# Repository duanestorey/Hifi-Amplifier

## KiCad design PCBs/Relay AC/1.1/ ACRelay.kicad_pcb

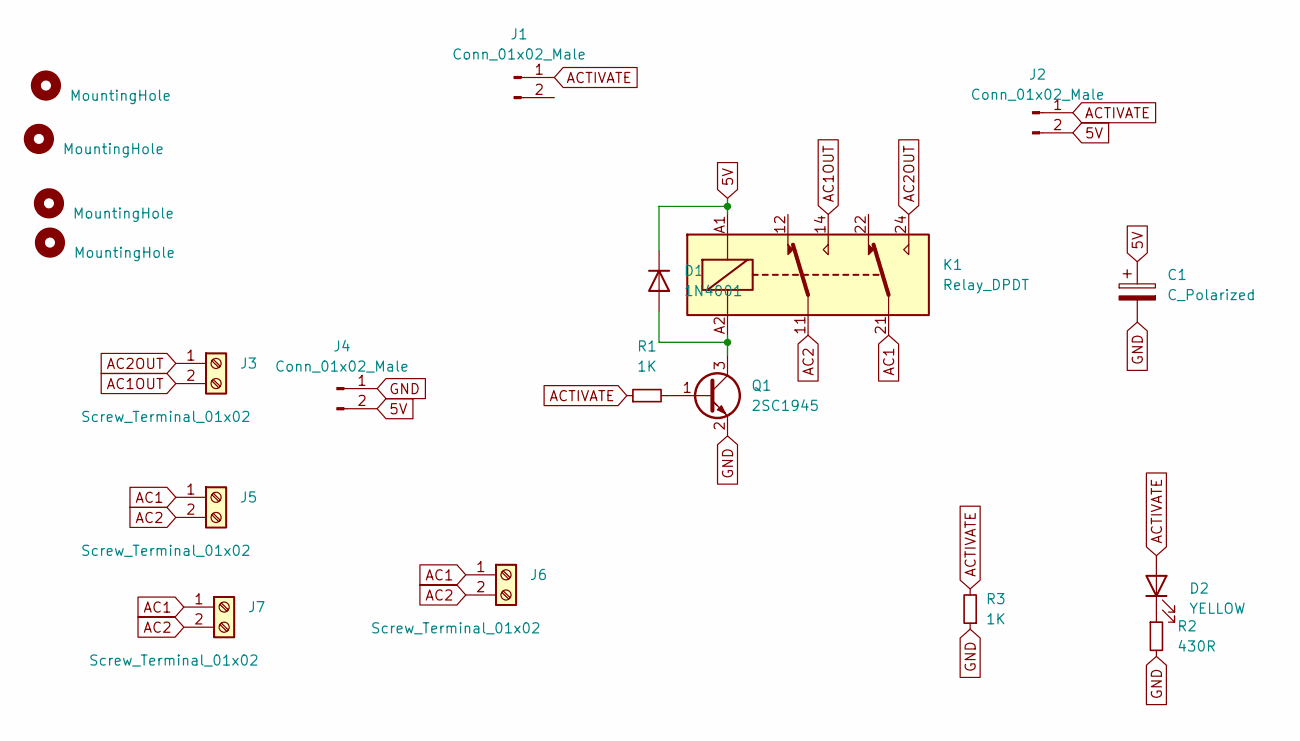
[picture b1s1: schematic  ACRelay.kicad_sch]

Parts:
C1: C_Polarized; CP_Radial_D6.3mm_P2.50mm
D1: 1N4001; D_SMA
D2: YELLOW; D_0805_2012Metric_Pad1.15x1.40mm_HandSolder
H1, H2, H3, H4: MountingHole; MountingHole_3.2mm_M3
J1, J4: Conn_01x02_Male; JST_PH_B2B-PH-K_1x02_P2.00mm_Vertical
J2: Conn_01x02_Male; PinHeader_1x02_P2.54mm_Vertical
J3, J5, J6, J7: Screw_Terminal_01x02; JST_XH_B2B-XH-A_1x02_P2.50mm_Vertical
K1: Relay_DPDT; Relay_DPDT_Omron_G2RL-2
Q1: 2SC1945; SOT-23_Handsoldering
R1, R3: 1K; R_0603_1608Metric
R2: 430R; R_0603_1608Metric_Pad0.98x0.95mm_HandSolder

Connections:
5V: C1.1, D1.1 (K), J2.2, J4.2, K1.A1
AC1: J5.1, J6.1, J7.1, K1.21
AC1OUT: J3.2, K1.14
AC2: J5.2, J6.2, J7.2, K1.11
AC2OUT: J3.1, K1.24
ACTIVATE: D2.2 (A), J1.1, J2.1, R1.1, R3.2
GND: C1.2, J4.1, Q1.2 (E), R2.2, R3.1
unnamed: D1.2 (A), K1.A2, Q1.3 (C)
unnamed: D2.1 (K), R2.1
unnamed: Q1.1 (B), R1.2

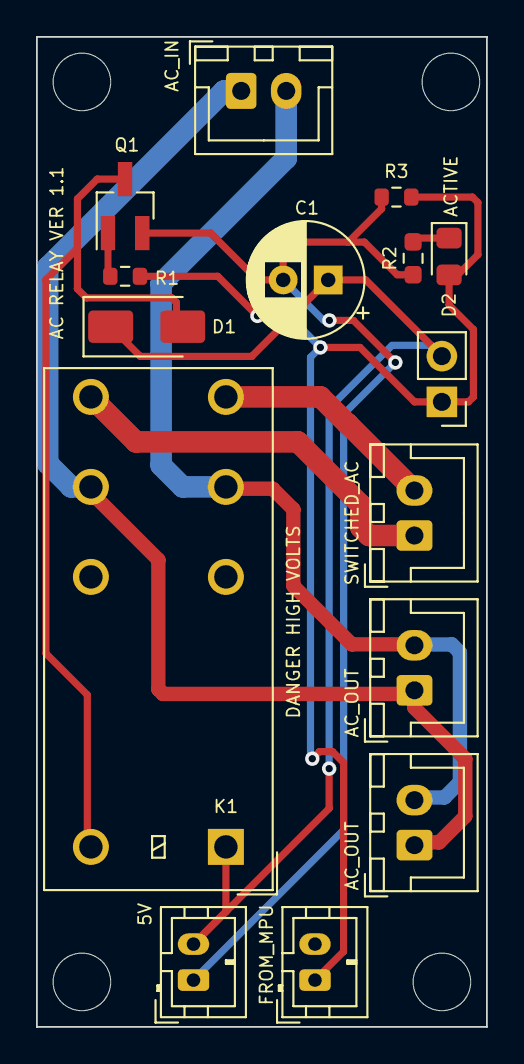
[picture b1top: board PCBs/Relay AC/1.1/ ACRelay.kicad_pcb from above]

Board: 2 copper layers, 25.0 x 55.0 mm, 19 parts (0 on the bottom side), 10 nets.

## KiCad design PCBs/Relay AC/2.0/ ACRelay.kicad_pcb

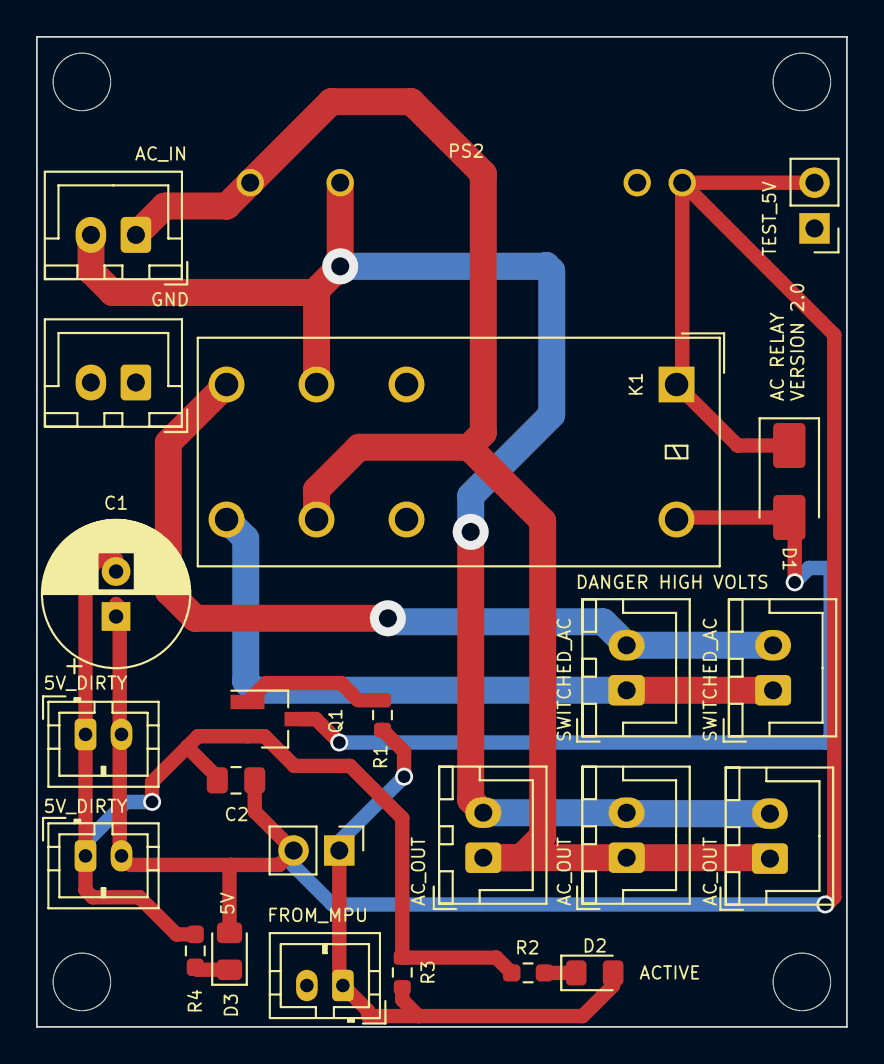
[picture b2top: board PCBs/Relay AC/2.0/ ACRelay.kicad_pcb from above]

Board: 2 copper layers, 45.0 x 55.0 mm, 28 parts (0 on the bottom side), 11 nets.

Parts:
C1: C_Polarized; CP_Radial_D8.0mm_P2.50mm
C2: 0.1u; C_0805_2012Metric_Pad1.18x1.45mm_HandSolder
D1: 1N4001; D_SMA
D2: YELLOW; D_0805_2012Metric_Pad1.15x1.40mm_HandSolder
D3: BLUE; D_0805_2012Metric_Pad1.15x1.40mm_HandSolder
H1, H2, H3, H4: MountingHole; MountingHole_3.2mm_M3
J1, J4, J10: Conn_01x02_Male; JST_PH_B2B-PH-K_1x02_P2.00mm_Vertical
J2, J12: Conn_01x02_Male; PinHeader_1x02_P2.54mm_Vertical
J3, J5, J6, J7, J8, J9, J11: Screw_Terminal_01x02; JST_XH_B2B-XH-A_1x02_P2.50mm_Vertical
K1: Relay_DPDT; Relay_DPDT_Omron_G2RL-2
PS2: HLK-2M05
Q1: 2SC1945; SOT-23_Handsoldering
R1, R3: 1K; R_0603_1608Metric
R2, R4: 1K; R_0603_1608Metric_Pad0.98x0.95mm_HandSolder

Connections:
5V: C1.1, C2.2, D1.1 (K), D3.2 (A), J2.2, J4.2, J10.2, J12.2, K1.A1, PS2.4 (+Vout)
AC1: J5.1, J6.1, J7.1, J9.1, K1.21, PS2.1 (AC/L)
AC1OUT: J3.2, J11.2, K1.14
AC2: J5.2, J6.2, J7.2, J9.2, K1.11, PS2.2 (AC/N)
AC2OUT: J3.1, J11.1, K1.24
ACTIVATE: D2.2 (A), J1.1, J2.1, R1.1, R3.2
unnamed: D1.2 (A), K1.A2, Q1.3 (C)
unnamed: D2.1 (K), R2.1
unnamed: D3.1 (K), R4.1
unnamed: Q1.1 (B), R1.2
PGND: C1.2, C2.1, J4.1, J8.1, J10.1, J12.1, PS2.3 (-Vout), Q1.2 (E), R2.2, R3.1, R4.2

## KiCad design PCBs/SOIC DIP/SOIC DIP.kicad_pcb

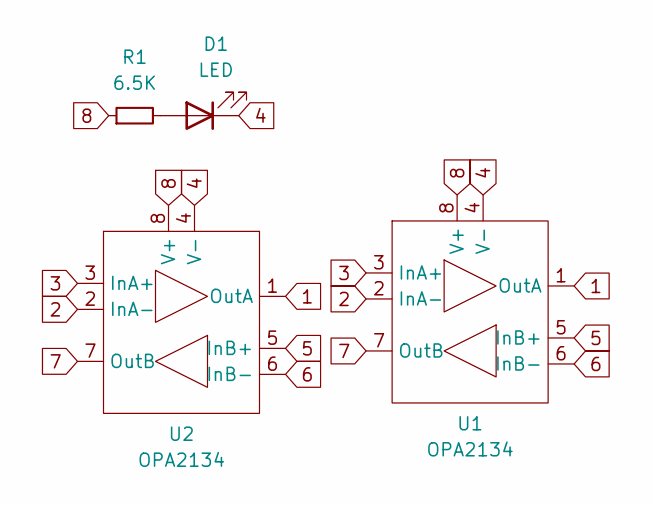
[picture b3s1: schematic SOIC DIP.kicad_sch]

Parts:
D1: LED; LED_0805_2012Metric_Pad1.15x1.40mm_HandSolder
R1: 6.5K; R_0805_2012Metric_Pad1.20x1.40mm_HandSolder
U1: OPA2134; DIP-8_W7.62mm_Socket
U2: OPA2134; SOIC-8_3.9x4.9mm_P1.27mm

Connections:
1: U1.1 (OutA), U2.1 (OutA)
2: U1.2 (InA-), U2.2 (InA-)
3: U1.3 (InA+), U2.3 (InA+)
4: D1.1 (K), U1.4 (V-), U2.4 (V-)
5: U1.5 (InB+), U2.5 (InB+)
6: U1.6 (InB-), U2.6 (InB-)
7: U1.7 (OutB), U2.7 (OutB)
8: R1.1, U1.8 (V+), U2.8 (V+)
unnamed: D1.2 (A), R1.2

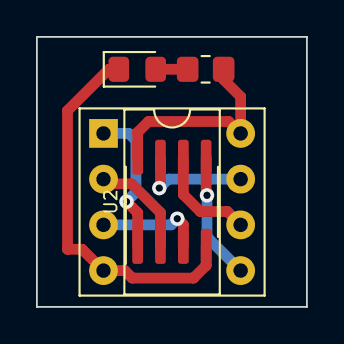
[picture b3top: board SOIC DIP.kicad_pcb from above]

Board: 2 copper layers, 15.0 x 15.0 mm, 4 parts (0 on the bottom side), 9 nets.

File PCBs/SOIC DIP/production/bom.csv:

Designator,Footprint,Quantity,Value,LCSC Part #
D1,LED_0805_2012Metric_Pad1.15x1.40mm_HandSolder,1,LED,
R1,R_0805_2012Metric_Pad1.20x1.40mm_HandSolder,1,6.5K,
U1,DIP-8_W7.62mm_Socket,1,OPA2134,
U2,SOIC-8_3.9x4.9mm_P1.27mm,1,OPA2134,

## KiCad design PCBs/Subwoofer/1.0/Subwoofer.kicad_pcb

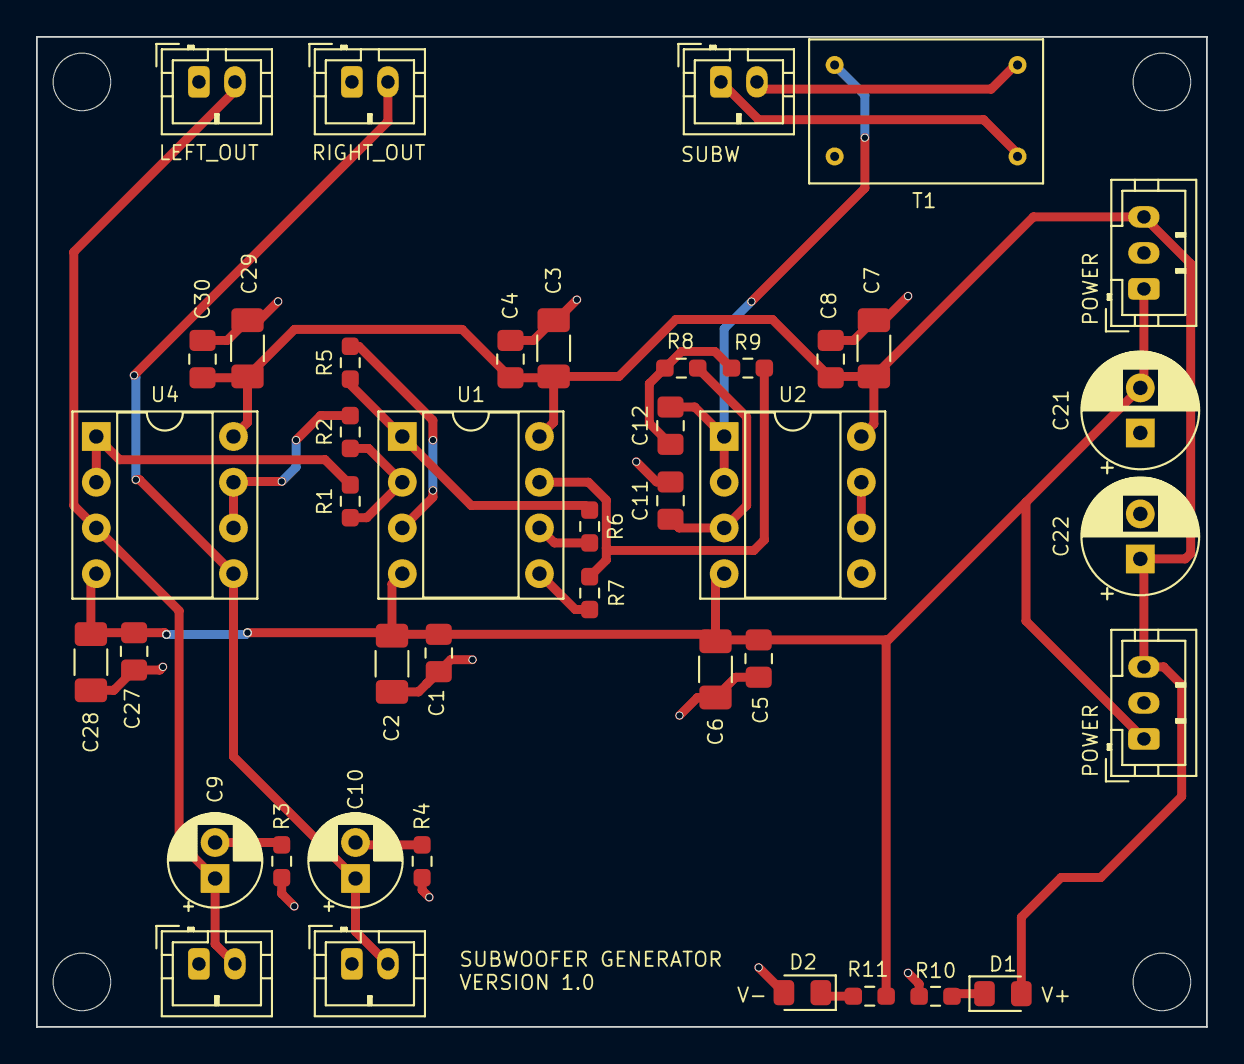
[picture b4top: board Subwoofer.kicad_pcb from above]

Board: 2 copper layers, 65.0 x 55.0 mm, 46 parts (0 on the bottom side), 23 nets.

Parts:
C1, C4, C5, C8, C27, C30: 0.1U; C_0805_2012Metric_Pad1.18x1.45mm_HandSolder
C2, C3, C6, C7, C28, C29: 10U; C_1206_3216Metric_Pad1.33x1.80mm_HandSolder
C9, C10: 10u; CP_Radial_D5.0mm_P2.00mm
C11: 56n C0G; C_0805_2012Metric_Pad1.18x1.45mm_HandSolder
C12: 130n C0G; C_0805_2012Metric_Pad1.18x1.45mm_HandSolder
C21, C22: 470u; CP_Radial_D6.3mm_P2.50mm
D1: YELLOW; LED_0805_2012Metric_Pad1.15x1.40mm_HandSolder
D2: BLUE; LED_0805_2012Metric_Pad1.15x1.40mm_HandSolder
H1, H2, H3, H4: MountingHole; MountingHole_3.2mm_M3
J1, J2, J4, J7, J15: Conn_01x02_Pin; JST_PH_B2B-PH-K_1x02_P2.00mm_Vertical
J3, J9: Conn_01x03_Male; JST_PH_B3B-PH-K_1x03_P2.00mm_Vertical
R1, R2, R3, R4, R6, R7: 10K; R_0603_1608Metric_Pad0.98x0.95mm_HandSolder
R5: 20K; R_0603_1608Metric_Pad0.98x0.95mm_HandSolder
R8: 23K; R_0603_1608Metric_Pad0.98x0.95mm_HandSolder
R9: 10.5K; R_0603_1608Metric_Pad0.98x0.95mm_HandSolder
R10: 1.25K; R_0603_1608Metric_Pad0.98x0.95mm_HandSolder
R11: 1K; R_0603_1608Metric_Pad0.98x0.95mm_HandSolder
T1: Transformer_Audio; DA101C
U1, U2, U4: OPA2134; DIP-8_W7.62mm_Socket

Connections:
AGND: C1.2, C2.2, C3.2, C4.2, C5.2, C6.2, C7.2, C8.2, C11.2, C21.1, C22.2, C27.2, C28.2, C29.2, C30.2, D2.2 (A), J1.1, J2.1, J3.2, J4.1, J9.2, J15.1, R3.1, R4.1, R10.1, T1.2 (AB), U2.5 (InB+)
COMBINED: R7.2, R9.2, U1.7 (OutB)
LEFT_BUF: R1.2, U4.1 (OutA), U4.2 (InA-)
LEFT_IN: C9.1, J1.2, J4.2, U4.3 (InA+)
unnamed: C9.2, R3.2
unnamed: C10.2, R4.2
unnamed: C12.1, R8.2, R9.1
unnamed: D1.1 (K), R10.2
unnamed: D2.1 (K), R11.2
unnamed: R5.2, U1.3 (InA+)
unnamed: R1.1, R2.1, U1.2 (InA-)
unnamed: R7.1, U1.5 (InB+)
unnamed: R6.2, U1.6 (InB-)
unnamed: R5.1, R6.1, U1.1 (OutA)
unnamed: C11.1, R8.1, U2.3 (InA+)
unnamed: U2.6 (InB-), U2.7 (OutB)
RIGHT_BUF: R2.2, U4.6 (InB-), U4.7 (OutB)
RIGHT_IN: C10.1, J2.2, J15.2, U4.5 (InB+)
SUBW: C12.2, T1.1 (AA), U2.1 (OutA), U2.2 (InA-)
SUBWN: J7.1, T1.3 (SA)
SUBWP: J7.2, T1.4 (SB)
V+: C3.1, C4.1, C7.1, C8.1, C22.1, C29.1, C30.1, D1.2 (A), J3.3, J9.3, U1.8 (V+), U2.8 (V+), U4.8 (V+)
V-: C1.1, C2.1, C5.1, C6.1, C21.2, C27.1, C28.1, J3.1, J9.1, R11.1, U1.4 (V-), U2.4 (V-), U4.4 (V-)

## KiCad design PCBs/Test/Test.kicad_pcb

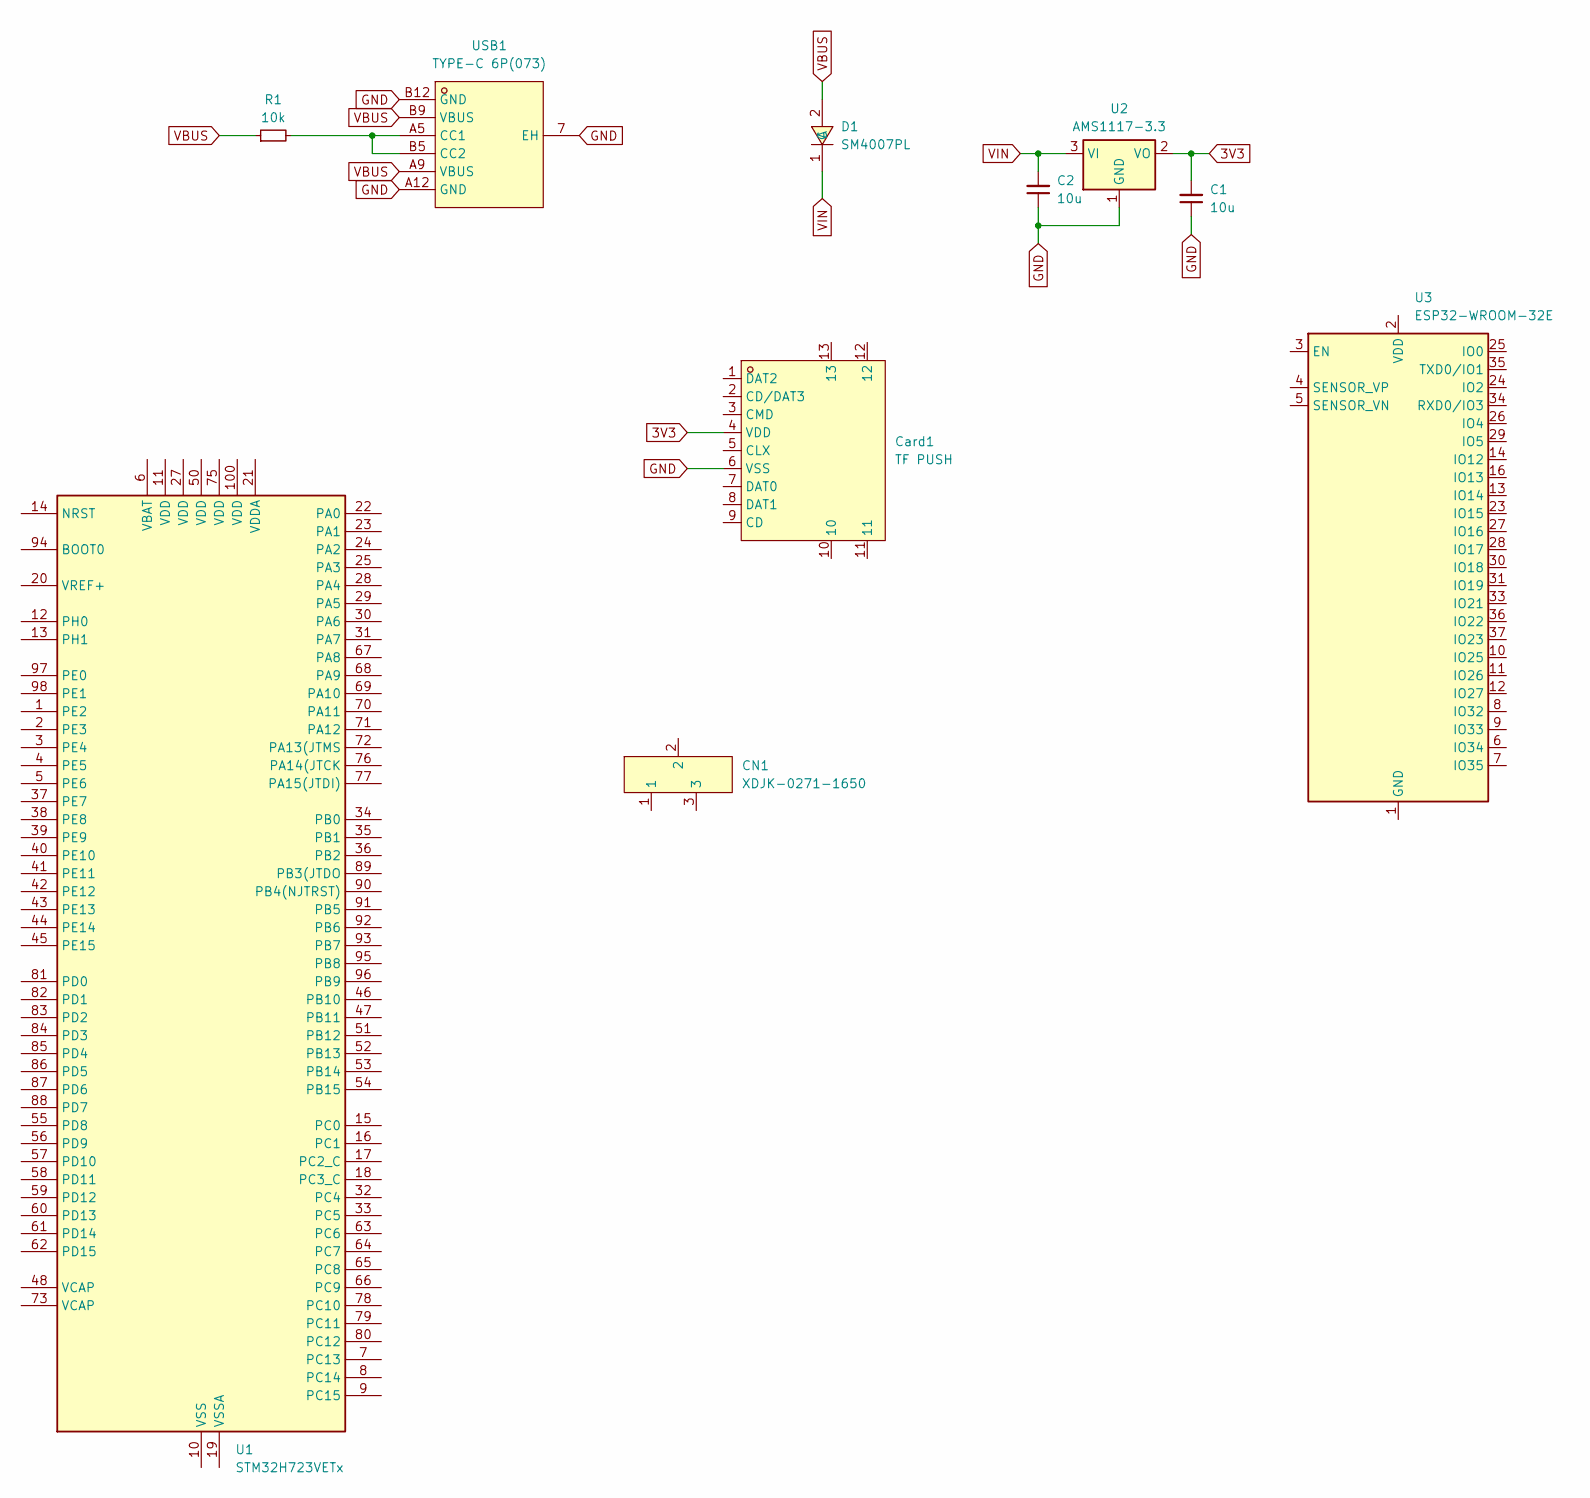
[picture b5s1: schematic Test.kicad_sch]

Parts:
C1, C2: 10u; C_0603_1608Metric; LCSC C57112
CN1: XDJK-0271-1650; CONN-TH_XDJK-0271-1650; LCSC Part C7527522
Card1: TF PUSH; TF-SMD_TF-PUSH; LCSC Part C393941
D1: SM4007PL; SOD-123F_L2.8-W1.8-LS3.7-RD; LCSC Part C64898
R1: 10k; R_0402_1005Metric; LCSC C25744
U1: STM32H723VETx; LQFP-100_14x14mm_P0.5mm; LCSC C730141
U2: AMS1117-3.3; SOT-223-3_TabPin2; LCSC C6186
U3: ESP32-WROOM-32E; ESP32-WROOM-32D; LCSC C701342
USB1: TYPE-C 6P(073); TYPE-C-SMD_TYPE-C-6P_5; LCSC Part C668623

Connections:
3V3: C1.2, Card1.4 (VDD), U2.2 (VO)
GND: C1.1, C2.1, Card1.6 (VSS), U2.1 (GND), USB1.7 (EH), USB1.A12 (GND), USB1.B12 (GND)
unnamed: U1.10 (VSS), U1.26 (VSS), U1.49 (VSS), U1.74 (VSS), U1.99 (VSS)
unnamed: U3.1 (GND), U3.15 (GND), U3.38 (GND), U3.39 (GND)
unnamed: R1.2, USB1.A5 (CC1), USB1.B5 (CC2)
VBUS: D1.2 (A), R1.1, USB1.A9 (VBUS), USB1.B9 (VBUS)
VIN: C2.2, D1.1 (C), U2.3 (VI)

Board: 2 copper layers, 10 parts (0 on the bottom side), 7 nets, no tracks yet.

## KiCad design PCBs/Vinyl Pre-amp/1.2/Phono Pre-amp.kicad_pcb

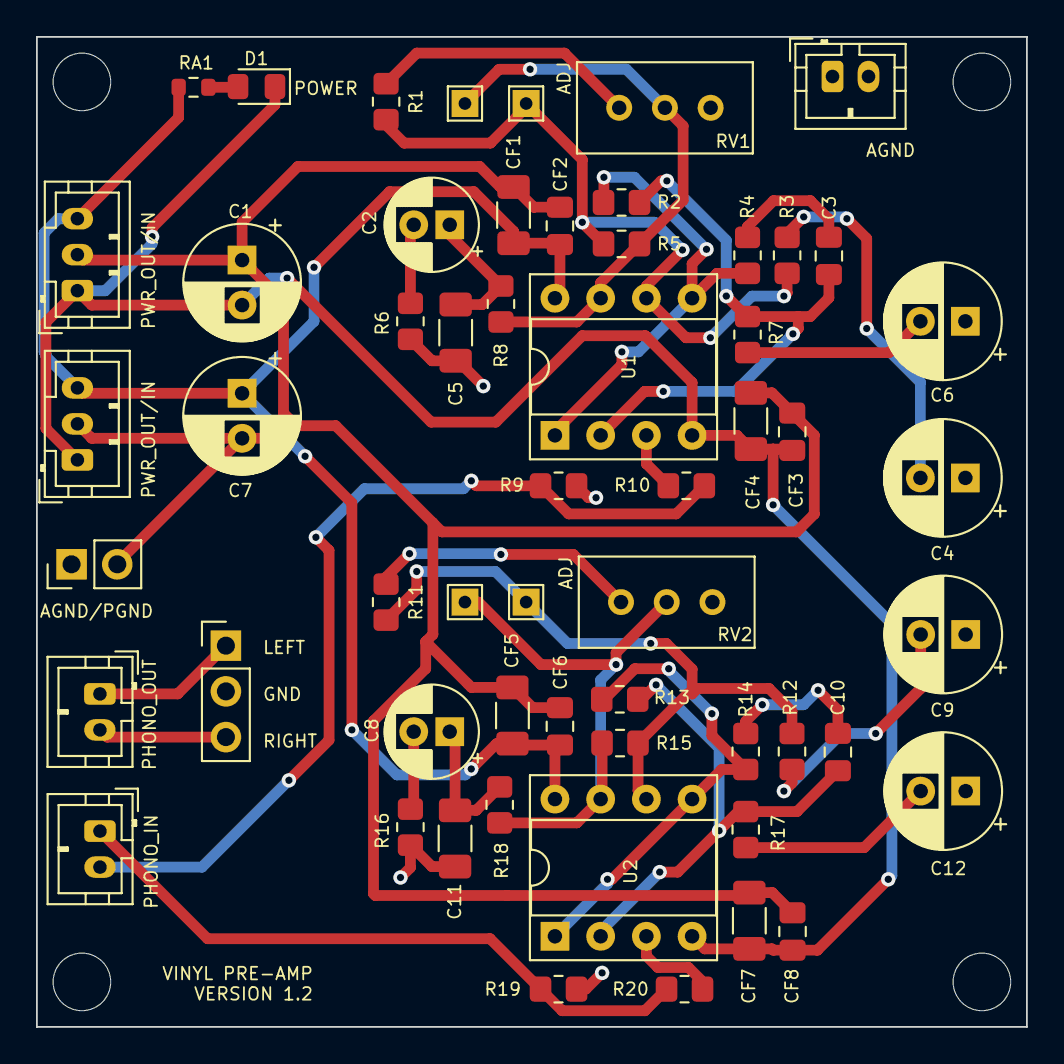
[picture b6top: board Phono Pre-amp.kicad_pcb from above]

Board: 2 copper layers, 55.0 x 55.0 mm, 61 parts (0 on the bottom side), 31 nets.

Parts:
C1, C7: 100U 16V; CP_Radial_D6.3mm_P2.50mm
C2, C8: 1U C0G; CP_Radial_D5.0mm_P2.00mm
C3, C10: 22N C0G; C_0805_2012Metric_Pad1.18x1.45mm_HandSolder
C4, C6, C9, C12: 22U; CP_Radial_D6.3mm_P2.50mm
C5, C11: 0.1U C0G; C_1206_3216Metric_Pad1.33x1.80mm_HandSolder
CF1, CF4, CF5, CF7: 10u; C_1206_3216Metric_Pad1.33x1.80mm_HandSolder
CF2, CF3, CF6, CF8: 0.1u; C_0805_2012Metric_Pad1.18x1.45mm_HandSolder
D1: YELLOW; LED_0805_2012Metric_Pad1.15x1.40mm_HandSolder
H1, H2, H3, H4: MountingHole; MountingHole_3.2mm_M3
J1, J2: Conn_01x03_Male; JST_PH_B3B-PH-K_1x03_P2.00mm_Vertical
J3: Conn_01x03_Male; PinHeader_1x03_P2.54mm_Vertical
J4, J5, J6: Conn_01x02_Male; JST_PH_B2B-PH-K_1x02_P2.00mm_Vertical
J7: Conn_01x02_Pin; PinHeader_1x02_P2.54mm_Vertical
R1, R11: 2.7K; R_0805_2012Metric_Pad1.20x1.40mm_HandSolder
R2, R13: 180K; R_0805_2012Metric_Pad1.20x1.40mm_HandSolder
R3, R12: 2K7; R_0805_2012Metric_Pad1.20x1.40mm_HandSolder
R4, R14: 10K; R_0805_2012Metric_Pad1.20x1.40mm_HandSolder
R5, R6, R15, R16: 100K; R_0805_2012Metric_Pad1.20x1.40mm_HandSolder
R7, R17: 4.7K; R_0805_2012Metric_Pad1.20x1.40mm_HandSolder
R8, R18: 750R; R_0805_2012Metric_Pad1.20x1.40mm_HandSolder
R9, R19: 47K; R_0805_2012Metric_Pad1.20x1.40mm_HandSolder
R10, R20: 2K2; R_0805_2012Metric_Pad1.20x1.40mm_HandSolder
RA1: 5.1K; R_0603_1608Metric
RV1, RV2: 50K; Potentiometer_Bourns_3296W_Vertical
TP1, TP2, TP3, TP4: TestPoint; TestPoint_THTPad_1.5x1.5mm_Drill0.7mm
U1, U2: OPA2134; DIP-8_W7.62mm_Socket

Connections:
AGND: C4.1, C5.1, C6.1, C9.1, C11.1, C12.1, J3.2, J6.1, J6.2, J7.1, R6.1, R9.1, R16.1, R19.1
LEFTAMP: C8.2, R16.2
LEFTIN: J5.1, R19.2, R20.1
LEFTOUT: J3.1, J4.1
unnamed: C2.1, C5.2, R8.1
unnamed: C3.2, R4.2
unnamed: C4.2, R3.1
unnamed: C6.2, R7.1
unnamed: C9.2, R12.1
unnamed: C10.2, R14.2
unnamed: C8.1, C11.2, R18.1
unnamed: C12.2, R17.1
unnamed: D1.2 (A), RA1.1
unnamed: R1.1, RV1.3
unnamed: R11.1, RV2.3
unnamed: R10.2, U1.3 (InA+)
unnamed: C3.1, R2.1, R7.2, U1.2 (InA-)
unnamed: R2.2, R4.1, U1.1 (OutA), U1.5 (InB+)
unnamed: R1.2, R3.2, R5.2, TP2.1, U1.6 (InB-)
unnamed: R5.1, R8.2, RV1.2, TP1.1, U1.7 (OutB)
unnamed: R20.2, U2.3 (InA+)
unnamed: C10.1, R13.1, R17.2, U2.2 (InA-)
unnamed: R13.2, R14.1, U2.1 (OutA), U2.5 (InB+)
unnamed: R11.2, R12.2, R15.2, TP4.1, U2.6 (InB-)
unnamed: R15.1, R18.2, RV2.2, TP3.1, U2.7 (OutB)
PGND: C1.1, C7.2, CF1.1, CF2.1, CF3.1, CF4.1, CF5.1, CF6.1, CF7.1, CF8.1, J1.2, J2.2, J7.2
RIGHTAMP: C2.2, R6.2
RIGHTIN: J5.2, R9.2, R10.1
RIGHTOUT: J3.3, J4.2
V+: C7.1, CF1.2, CF2.2, CF5.2, CF6.2, J1.3, J2.3, RA1.2, U1.8 (V+), U2.8 (V+)
V-: C1.2, CF3.2, CF4.2, CF7.2, CF8.2, D1.1 (K), J1.1, J2.1, U1.4 (V-), U2.4 (V-)

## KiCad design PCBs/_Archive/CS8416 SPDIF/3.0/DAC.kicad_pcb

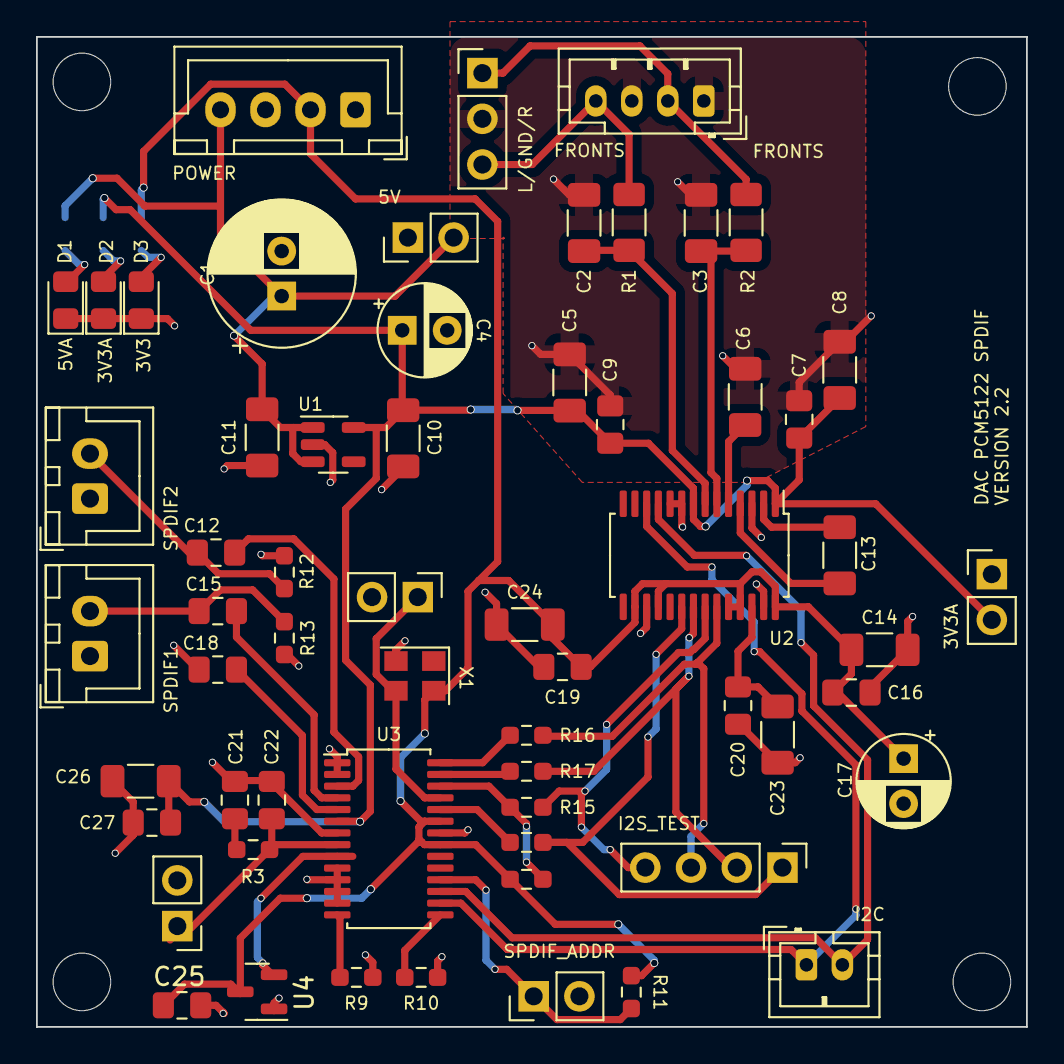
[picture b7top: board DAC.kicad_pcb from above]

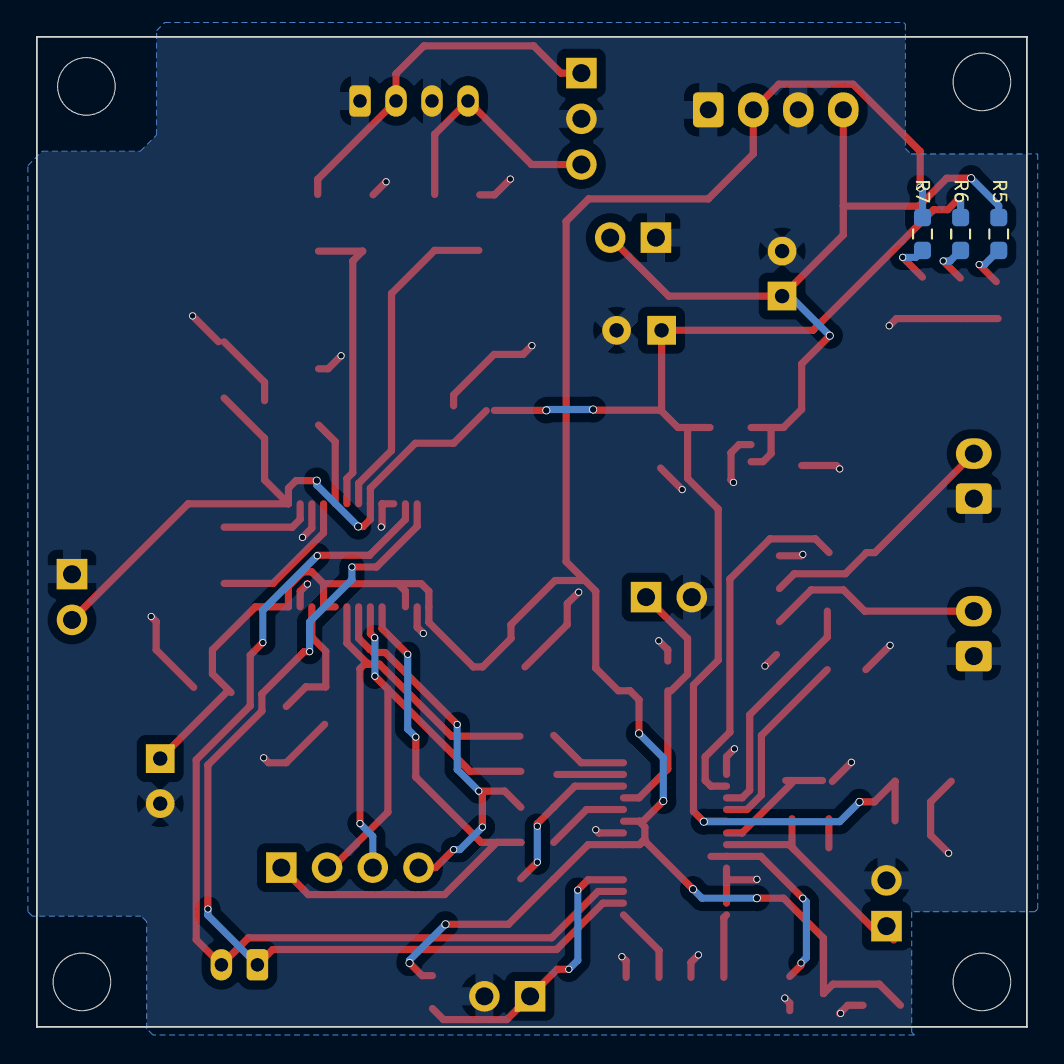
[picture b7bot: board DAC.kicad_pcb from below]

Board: 2 copper layers, 55.0 x 55.0 mm, 67 parts (3 on the bottom side), 37 nets.

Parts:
C1: 330u 16V; CP_Radial_D8.0mm_P2.50mm
C2, C3: 2.2n; C_1206_3216Metric_Pad1.33x1.80mm_HandSolder
C4, C17: 100u 16V; CP_Radial_D5.0mm_P2.50mm
C5, C8, C14, C23, C24, C26: 10u; C_1206_3216Metric_Pad1.33x1.80mm_HandSolder
C6, C13: 2.2u; C_1206_3216Metric_Pad1.33x1.80mm_HandSolder
C7, C9, C16, C19, C20, C25, C27: 0.1u; C_0805_2012Metric_Pad1.18x1.45mm_HandSolder
C10, C11: 1u; C_1206_3216Metric_Pad1.33x1.80mm_HandSolder
C12, C15, C18: 0.01u; C_0805_2012Metric_Pad1.18x1.45mm_HandSolder
C21: 22n; C_0805_2012Metric_Pad1.18x1.45mm_HandSolder
C22: 1n; C_0805_2012Metric_Pad1.18x1.45mm_HandSolder
D1: BLUE; LED_0805_2012Metric_Pad1.15x1.40mm_HandSolder
D2, D3: YELLOW; LED_0805_2012Metric_Pad1.15x1.40mm_HandSolder
H1, H2, H3, H4: MountingHole; MountingHole_3.2mm_M3
J1: Conn_01x03_Male; PinHeader_1x03_P2.54mm_Vertical
J2: Conn_01x04_Pin; PinHeader_1x04_P2.54mm_Vertical
J3: Conn_01x04_Pin; JST_XH_B4B-XH-A_1x04_P2.50mm_Vertical
J4: Conn_01x02_Male; JST_PH_B2B-PH-K_1x02_P2.00mm_Vertical
J6, J8, J11, J14, J15: Conn_01x02_Pin; PinHeader_1x02_P2.54mm_Vertical
J7, J9: Conn_01x02_Male; JST_XH_B2B-XH-A_1x02_P2.50mm_Vertical
J12: Conn_01x04_Pin; JST_PH_B4B-PH-K_1x04_P2.00mm_Vertical
R1, R2: 470R; R_1206_3216Metric_Pad1.30x1.75mm_HandSolder
R3: 3K; R_0603_1608Metric_Pad0.98x0.95mm_HandSolder
R5: 1K; R_0603_1608Metric_Pad0.98x0.95mm_HandSolder
R6, R7: 430R; R_0603_1608Metric_Pad0.98x0.95mm_HandSolder
R8: 47K; R_0603_1608Metric_Pad0.98x0.95mm_HandSolder
R9, R10, R11: 4.7K; R_0603_1608Metric_Pad0.98x0.95mm_HandSolder
R12, R13: 75R; R_0603_1608Metric_Pad0.98x0.95mm_HandSolder
R15, R16, R17, R18: 22R; R_0603_1608Metric_Pad0.98x0.95mm_HandSolder
U1: NCV8161; TSOT-23-5
U2: PCM5122PW; TSSOP-28_4.4x9.7mm_P0.65mm
U3: CS8416-xZZ; TSSOP-28_4.4x9.7mm_P0.65mm
U4: MCP130; SOT-23
X1: ASE-xxxMHz; Oscillator_SMD_Abracon_ASE-4Pin_3.2x2.5mm

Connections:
3V3: C14.1, C16.2, C17.1, C19.1, C24.1, C25.2, J3.2, R7.1, R8.2, R11.1, U2.16 (ADR2/GPIO2/DOUT), U2.18 (MODE2/MS), U2.24 (ADR1/MISO/FMT), U2.25 (XSMT), U2.28 (DVDD), U3.21 (VL), U3.23 (VD), U4.3 (VCC), X1.4 (Vdd)
3V3A: C4.1, C5.1, C7.2, C8.1, C9.1, C10.1, C26.2, C27.2, J6.2, R6.1, U1.5 (OUTPUT), U2.1 (CPVDD), U2.8 (AVDD), U3.6 (VA)
5V: C1.1, C11.1, J3.4, J8.2, R5.1, U1.1 (INPUT), U1.3 (EN)
AGND: C1.2, C2.1, C3.1, C4.2, C5.2, C6.1, C7.1, C8.2, C9.2, C10.2, C11.2, C14.2, C16.1, C17.2, C18.1, C19.2, C20.2, C21.2, C22.1, C23.2, C24.2, C25.1, C26.1, C27.1, D1.1 (K), D2.1 (K), D3.1 (K), J1.2, J3.1, J3.3, J6.1, J7.1, J8.1, J9.1, J11.2, J12.1, J12.3, J14.2, J15.2, R9.1, R10.1, R12.2, R13.2, U1.2 (GND), U2.3 (CPGND), U2.9 (AGND), U2.10 (VCOM/DEMP), U2.17 (MODE1), U2.27 (DGND), U3.1 (RXP3), U3.2 (RXP2), U3.7 (AGND), U3.10 (RXP4/RXSEL1), U3.11 (RXP5/RXSEL0), U3.12 (RXP6/TXSEL1), U3.13 (RXP7/TXSEL0), U3.22 (DGND), U4.1 (GND), X1.2 (GND)
FILT: C22.2, J15.1, R3.2, U3.8 (FILT)
I2S_BCLK: J2.2, R17.2, U2.21 (BCK)
I2S_DATA: J2.4, R15.2, U2.22 (DIN)
I2S_LRCLK: J2.3, R16.2, U2.23 (LRCK)
I2S_SCLK: J2.1, R18.2, U2.20 (SCK)
LEFT_FRONT: J1.1, J12.2, R2.1
unnamed: C21.1, R3.1
unnamed: D1.2 (A), R5.2
unnamed: D2.2 (A), R6.2
unnamed: D3.2 (A), R7.2
unnamed: J11.1, R11.2, U3.18 (U/AD2/GPO2)
unnamed: C13.1, U2.4 (CAPM)
unnamed: C13.2, U2.2 (CAPP)
unnamed: C20.1, C23.1, U2.26 (LDOO)
unnamed: C6.2, U2.5 (VNEG)
unnamed: R9.2, U3.14 (AD0/~CS/NV/RERR)
unnamed: R10.2, U3.15 (AD1/CDIN/~AUDIO)
unnamed: R16.1, U3.28 (OLRCK)
unnamed: R17.1, U3.27 (OSCLK)
unnamed: R18.1, U3.24 (RMCK)
unnamed: C18.2, U3.5 (RXN)
unnamed: C15.2, U3.4 (RXP0)
unnamed: C12.2, U3.3 (RXP1)
unnamed: R8.1, R15.1, U3.26 (SDOUT)
unnamed: U3.9 (~RESET), U4.2 (~RESET)
OMCK: J14.1, U3.25 (OMCK), X1.3 (OUT)
RIGHT_FRONT: J1.3, J12.4, R1.1
SCL: J4.1, U2.12 (SCL/MC/ATT1), U3.16 (SCL/CCLK/96KHZ)
SDA: J4.2, U2.11 (SDA/MOSI/ATT2), U3.17 (SDA/CDOUT/RCBL)
SPDIF_P1: C15.1, J9.2, R13.1
SPDIF_P2: C12.1, J7.2, R12.1
VOUT1: C3.2, R2.2, U2.6 (OUTL)
VOUT2: C2.2, R1.2, U2.7 (OUTR)
